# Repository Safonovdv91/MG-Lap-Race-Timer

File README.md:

# Проект MG-Lap-Race-Timer
Фотобарьер работающий на базе esp32-s3(или аналоги). Проектирование вед я создал проект, опиши мне подробную инструкцию по реализации схемы,
**MG-Lap-Race-Timer** — это система хронометража для спортивных мероприятий, использующая инфракрасные (ИК - TSAL6200, или аналог, Лазерный 940 нм) излучатель и фотодиод(BPW34, vishay ) для отслеживания времени круга и скорости. Система состоит из двух основных компонентов: **передатчика** и **приемника**, оба на базе микроконтроллера ESP32.

## Основные возможности

- **Измерение времени круга:** Точное отслеживание времени прохождения круга.
- **Измерение скорости:** Расчет скорости на основе времени пересечения луча.
- **Веб-интерфейс:** Удобный интерфейс для просмотра результатов в реальном времени, доступный с любого устройства с Wi-Fi.
- **Беспроводная телеметрия:** Передатчик отправляет данные о состоянии своей батареи на приемник.
- **Гибкая настройка:** Возможность изменения режимов работы и других параметров через веб-интерфейс.

## Архитектура

Система разделена на два устройства:

### 1. Передатчик (Transmitter)

- **Задача:** Генерировать постоянный ИК-сигнал или Laser-сигнал.
- **Функционал:**
  - ИК (LASER)-сигнал.
  - Измерение напряжения аккумулятора
  - Передача телеметрии(напряжение, вкл \выкл луч) по ESP-NOW на Receiver
  - Отображение заряда через LED
  - Hearbeat работы

 - **Принцип работы**
 - Шим сигнал ESP32 на GPIO13 D13 (частота 38кГц) через транзиcтор IRLZ44N.
  При duty = 50% использую х2 мощность(200мА) - TSAL6200

### 2. Приемник (Receiver)

- **Задача:** Обнаруживать пересечение ИК-луча и предоставлять интерфейс для пользователя.
- **Функционал:**
  - Создает точку доступа Wi-Fi.
  - Запускает веб-сервер, доступный по адресу `http://192.168.4.1`.
  - Регистрирует пересечение ИК(лазерного)-луча.
  - Рассчитывает время круга.
  - Отображает историю измерений.
  - Принимает и отображает данные телеметрии от передатчика.
  - Трансляция ESP-NOW с данными времени.

## Веб-интерфейс

Приемник предоставляет веб-интерфейс со следующими возможностями:

- **Выбор режима:**
  - **Секундомер круга (Lap Timer):** Измеряет время между двумя последовательными пересечениями одного датчика.
  - **Гоночный таймер (Race Timer):** Работает как стандартный секундомер, запускаемый первым датчиком и останавливаемый вторым.
- **Отображение данных:** Показывает текущее измерение, историю последних 5 измерений, а также состояние батарей приемника и передатчика.
- **Настройки:** Позволяет изменять расстояние между датчиками ( для режима спидометра) и настраивать параметры Wi-Fi.

## Аппаратное обеспечение

- **Микроконтроллер:** ESP32 DevKit V1 (или аналогичный).
- **Передатчик:** 
  - ИК-светодиоды(940нМ), laser излучатель.
  - Mosfet AO3400A, IRFL44N
  - TSAL6200. R1 = 100 Ом (Или из расчета пот току(обычно меньше 40мА)) В KY-008 не требуется.
- **Приемник:**
  - Светодиод BPW34 | Laser Detector | Vishay BPV10NF
  - Операционный усилитель - **LM358** / TLV2371 / OPA380.
  - Компаратор - **LM393** / LMV358
- **Обвязка:**
  - R:
    - 220 Ом
    - 2х 100 кОм
    - 1 МОм
  - C:
    - 0.1 мкФ 16В
    - 100 пФ
- **Источник питания:** 
  - Li-ion или Li-po аккумулятор. с повышающим модулем до 5В.
  - power boost li-ion -> 5В
  - Преобразователь 5В -> 3.3 В
  
### Схема подключения (пины)

#### Передатчик:

- `GPIO13 (D13)`: ИК-передатчик 1
- `GPIO34`: Датчик напряжения батареи(через делитель напряжения)

#### Приемник:

- `GPIO14`: ИК-приемник 1
- `GPIO34`: Датчик напряжения батареи(через делитель напряжения)

```
     (+) Батареи LiPo
           |
           |
         [ R1 ]  (1 МОм)
           |
           |---------------------> к пину GPIO 34 на ESP32
           |
         [ R2 ]  (300 кОм)
           |
           |---------------------> к пину GND (земля) на ESP32
           |
         [ C1 ]  (0.1 µF (100 nF) X7R 16 V или 25 V, керамика)
           |
            +---------------------> к пину GND (земля) на ESP32 (вторая нога конденсатора)
```

- `GPIO32 (D32)`: Светодиод статуса ( пересечения луча)
- `GPIO33 (D33)`: Светодиод режима измерений (запущен \ остановлен таймер)

## Сборка и прошивка

Проект использует [PlatformIO](https://platformio.org/).

1. **Установите PlatformIO Core** или [PlatformIO IDE for VSCode](https://platformio.org/install/ide?install=vscode).
2. Откройте проект в VSCode.
3. Для сборки и прошивки **передатчика** используйте команду:
   ```bash
   pio run -e transmitter -t upload
   ```
4. Для сборки и прошивки **приемника** используйте команду:
   ```bash
   pio run -e receiver -t upload
   ```

## Дальнейшее развитие

Проект имеет потенциал для улучшений:
- Добавление поддержки нескольких передатчиков.
- Сохранение истории измерений в энергонезависимой памяти.
- Улучшение безопасности веб-интерфейса.
- Оптимизация энергопотребления.

Элементная база:
esp32 devkit 30pin - основной модуль обработки логики, используется 
Точечный ИК-фотодиод Vishay BPV10NF для отслеживания пересечения луча
LM358P - усилитель сигнала луча
LM393N - компаратор для получения логического уровня и передача логического сигнала после сравнения с заданным сигналом и сигналом после LM358P
MT3608 - модуль заряда и питания, с выводом 5В. Запитан от LiIon21700 4500mAh
LM117T - если необходим можно использовать
Светодиоды для отображения логики(информация для отображения)

Подключение к ESP32:
GPIO13 - Выход LM393N
GPIO32 - светодиод 1
GPIO33 - светодиод 2

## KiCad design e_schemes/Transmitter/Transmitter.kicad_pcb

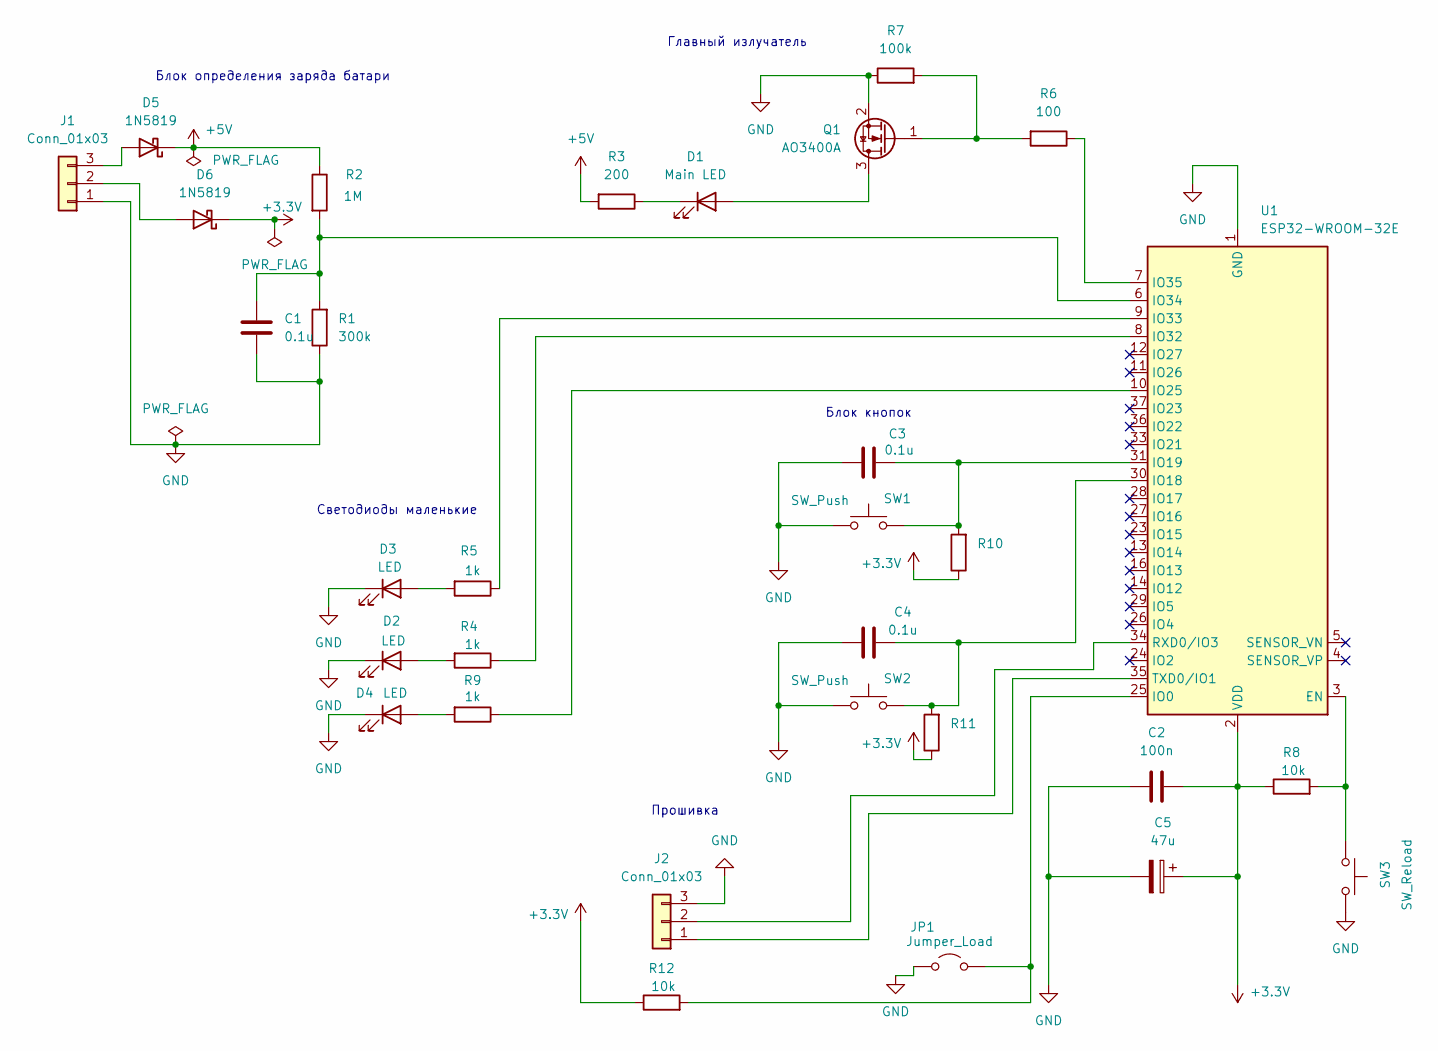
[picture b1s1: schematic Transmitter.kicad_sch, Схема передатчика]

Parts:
C1, C3, C4: 0.1u; C_Disc_D3.0mm_W1.6mm_P2.50mm
C2: 100n; C_Disc_D3.0mm_W1.6mm_P2.50mm
C5: 47u; C_Disc_D3.0mm_W1.6mm_P2.50mm
D1: Main LED; Osram_BPW82
D2, D3, D4: LED; D_DO-34_SOD68_P2.54mm_Vertical_KathodeUp
D5, D6: 1N5819; D_DO-41_SOD81_P10.16mm_Horizontal
J1: Conn_01x03; Hirose_DF63M-3P-3.96DSA_1x03_P3.96mm_Vertical
J2: Conn_01x03; FanPinHeader_1x03_P2.54mm_Vertical
JP1: Jumper_Load; Jumper_Harwin_S1621_P10.9mm
Q1: AO3400A; SOT-23
R1: 300k; R_Axial_DIN0204_L3.6mm_D1.6mm_P7.62mm_Horizontal
R2: 1M; R_Axial_DIN0204_L3.6mm_D1.6mm_P7.62mm_Horizontal
R3: 200; R_Axial_DIN0204_L3.6mm_D1.6mm_P7.62mm_Horizontal
R4, R5, R9: 1k; R_Axial_DIN0204_L3.6mm_D1.6mm_P7.62mm_Horizontal
R6: 100; R_Axial_DIN0204_L3.6mm_D1.6mm_P7.62mm_Horizontal
R7: 100k; R_Axial_DIN0204_L3.6mm_D1.6mm_P7.62mm_Horizontal
R8, R10, R11, R12: 10k; R_Axial_DIN0204_L3.6mm_D1.6mm_P7.62mm_Horizontal
SW1, SW2: SW_Push; SW_PUSH_1P1T_6x3.5mm_H5.0_APEM_MJTP1250
SW3: SW_Reload; SW_PUSH_1P1T_6x3.5mm_H5.0_APEM_MJTP1250
U1: ESP32-WROOM-32E

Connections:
+3.3V: C2.2, C5.1, D6.1 (K), R8.1, R10.1, R11.1, R12.1, U1.2 (VDD)
+5V: D5.1 (K), R2.1, R3.2
GND: C1.2, C2.1, C3.1, C4.1, C5.2, D2.1 (K), D3.1 (K), D4.1 (K), J1.1, J2.3, JP1.1 (A), Q1.2 (S), R1.1, R7.1, SW1.1, SW2.1, SW3.2, U1.1 (GND), U1.15 (GND), U1.38 (GND), U1.39 (GND); also elsewhere on the board
unnamed: D1.2 (A), Q1.3 (D)
unnamed: D1.1 (K), R3.1
unnamed: D2.2 (A), R4.2
unnamed: D3.2 (A), R5.2
unnamed: D4.2 (A), R9.2
unnamed: D5.2 (A), J1.3
unnamed: D6.2 (A), J1.2
unnamed: J2.1, U1.35 (TXD0/IO1)
unnamed: J2.2, U1.34 (RXD0/IO3)
unnamed: JP1.2 (B), R12.2, U1.25 (IO0)
unnamed: Q1.1 (G), R6.2, R7.2
unnamed 14: R8.2, SW3.1, U1.3 (EN); also elsewhere on the board
unnamed: C4.2, R11.2, SW2.2, U1.30 (IO18)
unnamed: C3.2, R10.2, SW1.2, U1.31 (IO19)
unnamed: R9.1, U1.10 (IO25)
unnamed: R4.1, U1.8 (IO32)
unnamed: R5.1, U1.9 (IO33)
unnamed: C1.1, R1.2, R2.2, U1.6 (IO34)
unnamed: R6.1, U1.7 (IO35)

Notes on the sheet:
Светодиоды маленькие
Прошивка
Блок кнопок
Главный излучатель
Блок определения заряда батари

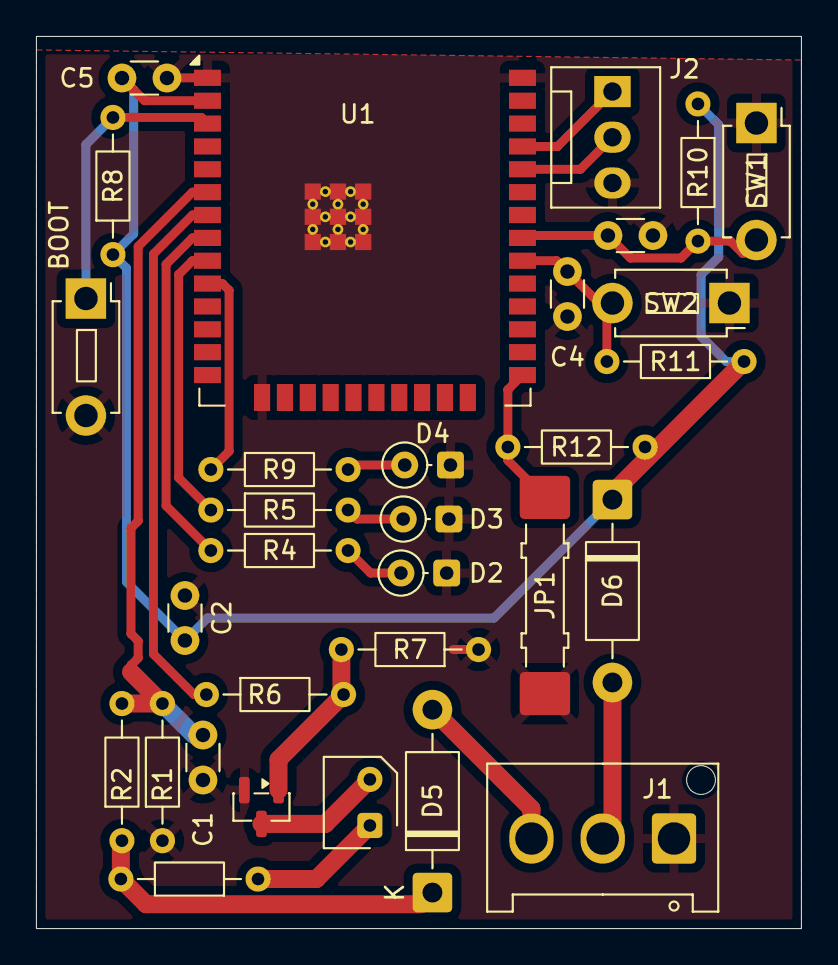
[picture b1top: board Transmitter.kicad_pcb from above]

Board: 2 copper layers, 42.5 x 49.6 mm, 31 parts (0 on the bottom side), 22 nets.

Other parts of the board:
BOOT: SW_Reload; SW_PUSH_1P1T_6x3.5mm_H5.0_APEM_MJTP1250

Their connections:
GND: BOOT.2; also elsewhere on the board
unnamed 14: BOOT.1; also elsewhere on the board

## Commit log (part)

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2025-05-29 Create ESP32 Lap Timer
    init
2025-05-29 Rename ESP32 Lap Timer to ESP32 Lap Timer.h
2025-05-29 Налаженно расположение файлов, чтобы Arduino IDE не ругалось
2025-06-10 Переделано все на VSCode и Platformio
2025-06-10 ADD: последовательный вывод истории изменений
2025-06-11 ADD: Отображение времени в формате mm:ss.ms Анимация отображения замеров вывод последовательно истории замеров
2025-06-11 ref:
2025-07-03 ADD: Добавлено отображение сработки датчиков пересечения луча
2025-07-22 rm blink
2025-07-22 ADD: Добавлена DNS запись
2025-07-25 ADD: Добавлена возможность смены SSID, pass для wi-fi
2025-07-25 REF: вебконтент настройки wifi в отдельный файл
2025-07-28 ADD: Добавлено отображение данных таймера в ральном времени. Добавлена задержка между измерениями 5секунд
2025-07-28 ADD: Подсветка сработавших датчиков 3сек
2025-07-28 REF: ручки переписаны на api пути.
2025-07-29 ADD: Добавлено отображение заряда батареи
2025-07-30 ADD: Коммутация датчиков через +3.3 В( NPN NO)
2025-08-28 ADD: Рекомендация по используемым пинам подключения датчиков.
2025-08-29 Использованы D14 D27 для получаения данных датчика
2025-08-31 REF: Изменено время задержки срабатывания датчиков пересечения и минимальное время круга до 1 сек
2026-01-15 FIX: Использование атомарных операций для доступа к общим переменным для исключения "гонки даных" при одновременном доступе из прерываний и основного цикла.
2026-01-15 FIX: Проблемы с утечкой памяти. использование статичное выделение памяти вместо динамического (strdup())
2026-01-15 FIX: решение проблемы потенциального переполнения при работе с микросекунлдами - добавлены механизмы синхронизации для безопасного доступа к переменным из разных частей программы.
2026-01-15 FIX: отображения времения в веб интерфейсе
2026-01-15 FIX: переменные исправлены на long long для исключения возможности переполнения.
2026-01-15 ADD: readme
2026-01-16 BUG FIX: исправление ошибки std::atomic
2026-01-16 FEAT: Пределан принцип работы на работу с IR светодиодами TSOP 38khz.
2026-01-16 ADD: Разделение на 2 датчика Излучатель / приемник
2026-01-18 FEAT: Переработан дизайн на работу кругового таймера, обновлен дизайн страницы
2026-01-18 ADD: Добавлен селектор выбора режима работы
2026-01-18 BUGFIX: оптимизация памяти вызывающая зависание процессора
2026-01-19 dev: В консоль выводится правильные значения таймера, но в UI поломался "Живой таймер".
2026-01-19 FIX: проблемы живого таймера
2026-01-19 FIX: 1) Устранена фрагментация памяти веб страницы перенесены в FS отдел памяти и не генерируется процесосром 2) TX в случае невозхможности подключения трансмиттер просто продолжает работать как пере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
2026-01-19 REF: Удаление неиспользуеммых переменных, в данный момент работает режи LapTimer Only.
2026-01-23 add: Components size
2026-01-26 FIX: После остановки таймера - режим остывания 5 секунд, показания не принимаются, так же добавлен индикатор
2026-01-26 ADD: Переписан код на использование вебсокетов для отображения таймера реал-тайм
2026-01-27 REF: Переделана формула расчета заряда батареи,используются менее энергозатратные резисторы с возможностью изменения сопротивления
2026-01-27 ADD: Добавлен светодиод с отображением работы хрономентрии на ГПИО 34
2026-01-28 ADD: Добавлено моргание светодиода при финише.
2026-01-28 refactoring: проблема с общим доступом к данным при добавлении в историю заездов
2026-01-28 feat: рассчет заряда аккумулятора через коэфф (начальная калибровка)
2026-01-29 калибровка батареи
2026-01-30 REF: Вынос рассчета аккумулятора в отдельныее файлы. геттеры для получения данных о заряде аккумулятора и напряжении
2026-02-01 REF: использования функции батарии для передатчика + рефакторинг
2026-02-01 ADD: Скрипт который не дает погаснуть экрану(not work)
2026-02-06 ADD: Спектограмма лазера
2026-02-08 ADD: Test нахождения длительности пачки до того как TSOP
2026-02-08 ADD: Описание websocket связи
2026-02-10 FEAT: переход на режим постоянного свечения, т.к. меняется концепция(не модуляция сигнала а постоянное его присутствие)
2026-02-10 macbook settings
2026-02-10 Оладка режима получения с батарейки
2026-02-10 UPDATE: Обновлена информация по передатчику.
2026-02-12 DEL: Удалена модуляция с TSOP
2026-02-12 Refactoring: Удаление лишних файлов т..к архитектурное решение через TSOP зашло в тупик
2026-02-13 Черновик
2026-02-13 ADD: заготовка схемы для трассировки
2026-02-14 ADD: добавлена распиновка
2026-02-15 ADD: Добавлены электросхемы
2026-02-16 ADD: Схема приемника
2026-02-16 ADD: (processed) Добавление светодиода состояния\
2026-02-18 Feat: добавлен светодиод состояния луча + рефакторинг(убрана функция спидометра)
2026-02-18 UPDATE: схема RX
2026-02-19 FIX: Чистка кода
2026-02-19 Bugfix: фикс двойного чтения статуса
2026-02-19 FIX: отображение статуса при конце круга.
2026-02-20 Отрисовка схемы
2026-02-20 FIX: получение текущего значения времени и статуса сенсора через безопасную функцию.
2026-02-20 REFactoring
2026-02-24 ref: удаление serial значений при получении данных батареи
2026-02-24 REF: Раделение логики UI и core, side_effects вынесены в отдельные функции.
2026-02-24 ADD: размер пакета ws
2026-02-24 rx scheme1
2026-02-25 REF: цпрощение отправки html страницы, и обновление динамических данных через JS + ws
2026-02-25 ADD: Установка пароля точки доступа через страницу настроек. Добавление UTF-8. Сохранение пароля в eeprom
2026-02-25 INIT: ESP-NOW
2026-02-26 Получение значений аккумулятора через ESP-NOW между двумя esp32
2026-02-26 FEAT: Переделана формула расчета заряда батареи average -> EMA.
2026-02-26 REF: удаление дублирующего кода, UDP устаревшего
2026-02-27 ADD: добавление broadcast рассылки данных
